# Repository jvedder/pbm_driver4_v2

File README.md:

# pdm_driver4_v2
 
PCB Design in KiCad 10 with 4 channels of high-speed, current-controlled LED drivers for a PBM Device prototype.
 
**MIT License**
 
**WARNING**: The eye safety of this device has not been established. **USE AT YOUR OWN RISK.**

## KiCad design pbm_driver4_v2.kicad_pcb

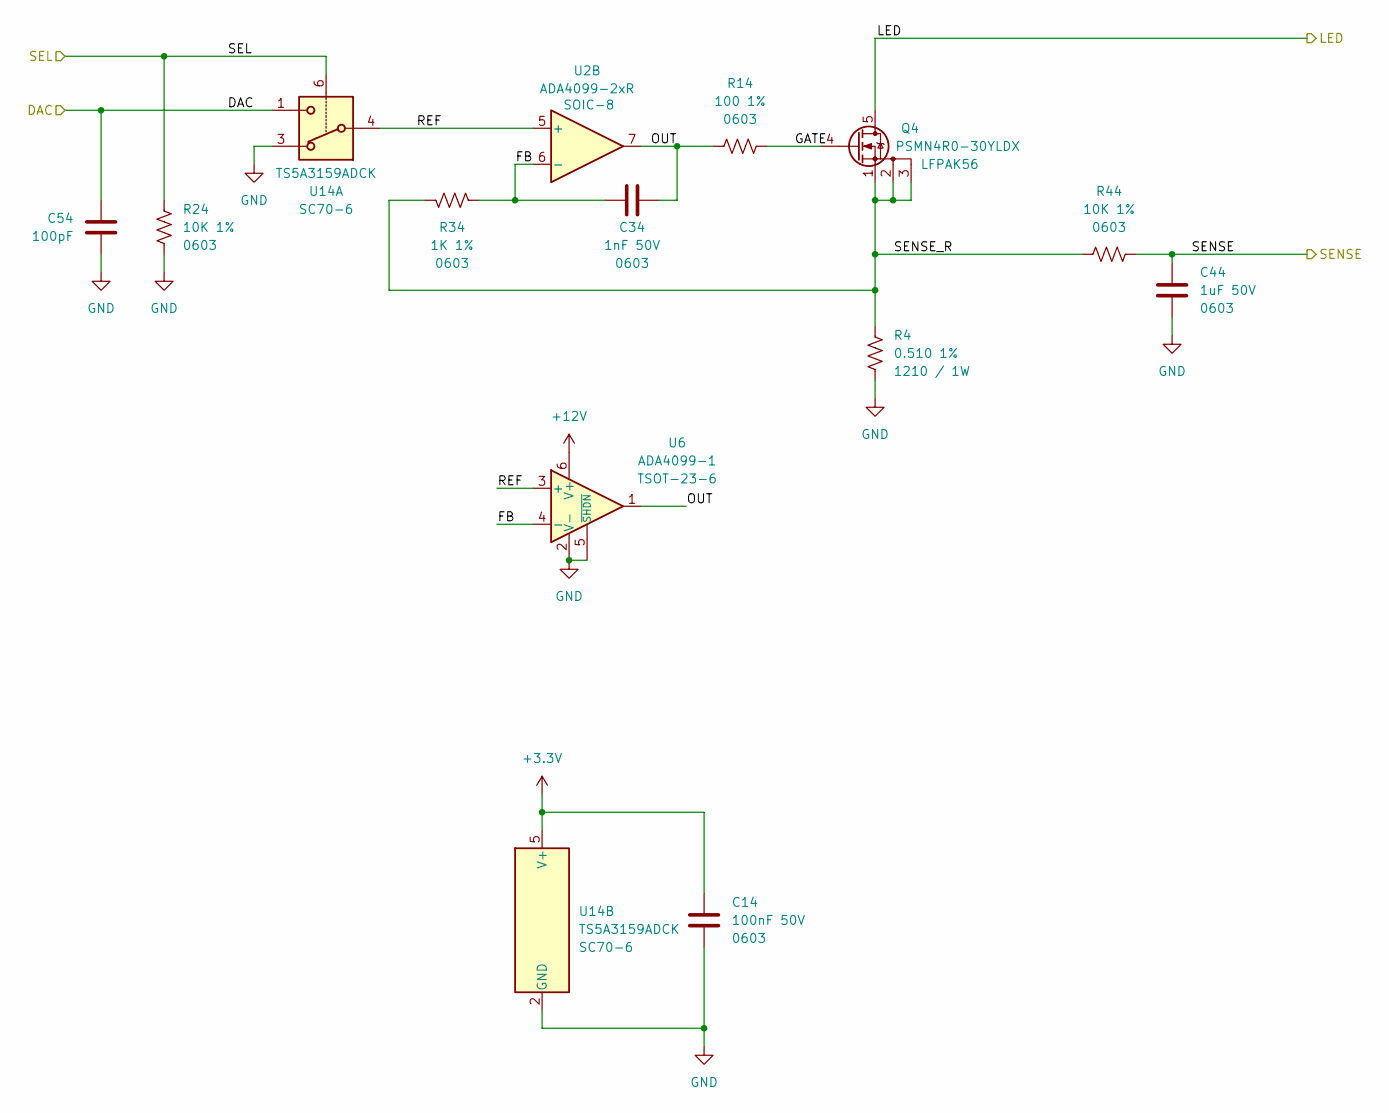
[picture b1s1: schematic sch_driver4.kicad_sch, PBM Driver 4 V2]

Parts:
C14: 100nF 50V; C_0603_1608Metric
C34: 1nF 50V; C_0603_1608Metric
C44: 1uF 50V; C_0603_1608Metric
C54: 100pF; C_0603_1608Metric
Q4: PSMN4R0-30YLDX; LFPAK56
R4: 0.510 1%; R_1210_3225Metric_Pad1.30x2.65mm_HandSolder
R14: 100 1%; R_0603_1608Metric
R24, R44: 10K 1%; R_0603_1608Metric
R34: 1K 1%; R_0603_1608Metric
U2: ADA4099-2xR; SOIC-8_3.9x4.9mm_P1.27mm; Digikey 505-ADA4099-2BRZ-ND
U6: ADA4099-1; TSOT-23-6; Digikey 505-ADA4099-1BUJZ-RL7CT-ND
U14: TS5A3159ADCK; SOT-363_SC-70-6; Digikey 296-21188-1-ND

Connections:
+3.3V: C14.1, U14.5 (V+); also elsewhere on the board
/DAC2: C54.1, U14.1; also elsewhere on the board
/Driver4/FB: C34.1, R34.2, U2.6 (-), U6.4 (-)
/Driver4/GATE: Q4.4 (G), R14.2
/Driver4/OUT: C34.2, R14.1, U2.7, U6.1
/Driver4/REF: U2.5 (+), U6.3 (+), U14.4
/Driver4/SENSE_R: Q4.1 (S), Q4.2 (S), Q4.3 (S), R4.1, R34.1, R44.2
/LED4: Q4.5 (D); also elsewhere on the board
/SEL4: R24.1, U14.6; also elsewhere on the board
/SENSE4: C44.1, R44.1; also elsewhere on the board
GND: C14.2, C44.2, C54.2, R4.2, R24.2, U6.2 (V-), U6.5 (~SHDN), U14.2 (GND), U14.3; also elsewhere on the board

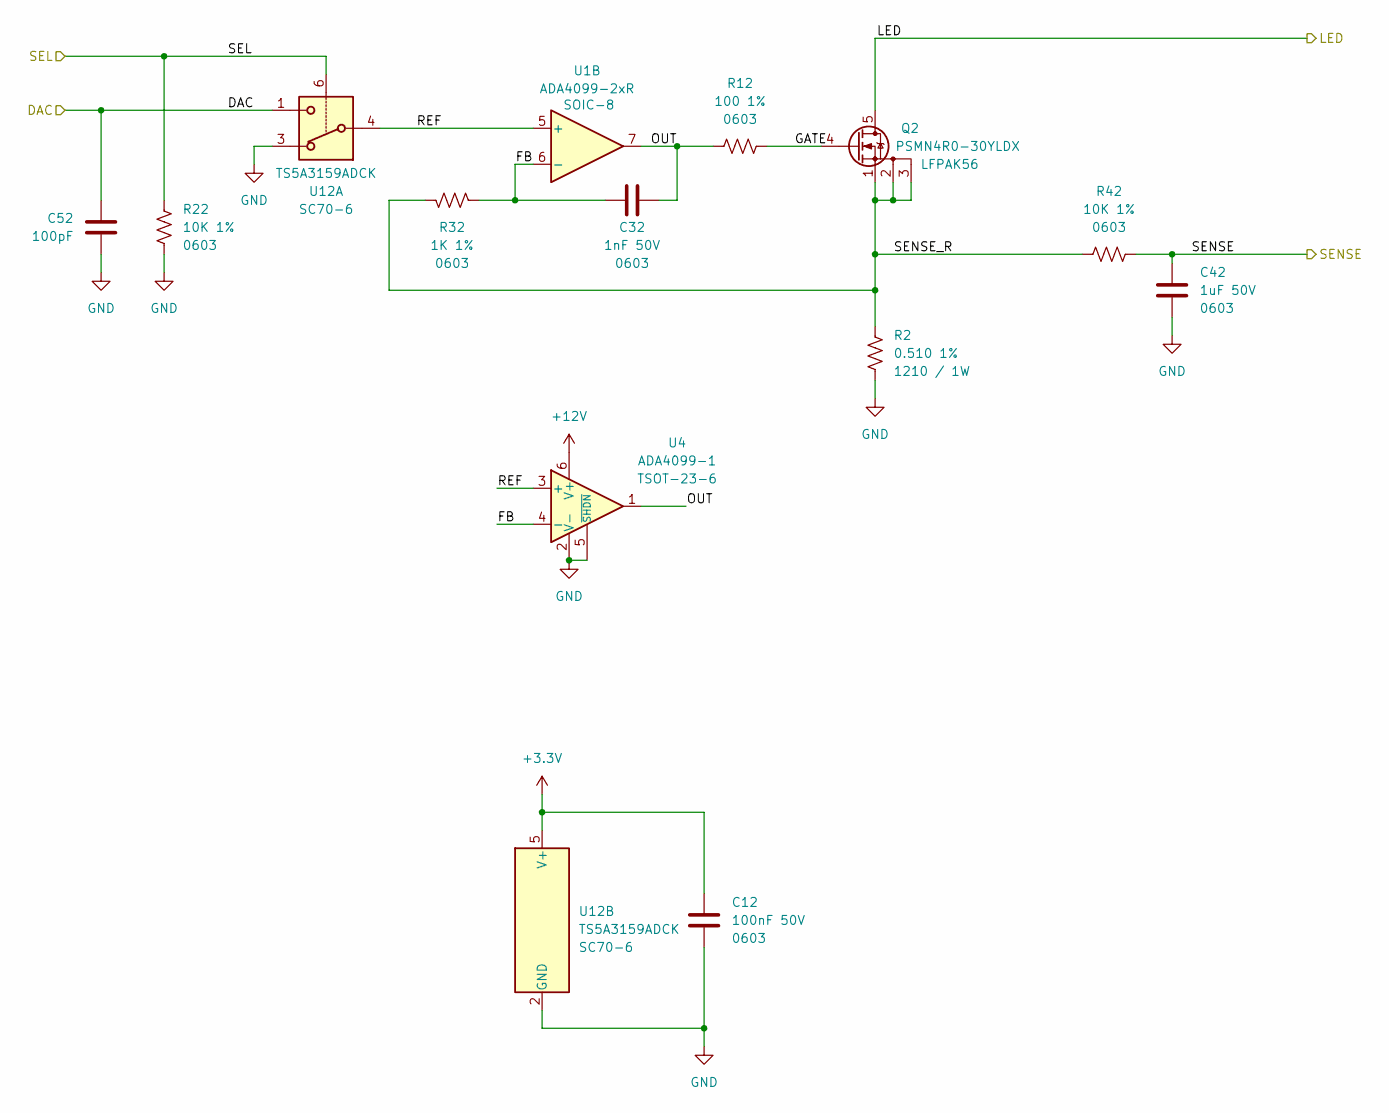
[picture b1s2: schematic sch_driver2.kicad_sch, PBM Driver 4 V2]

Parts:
C12: 100nF 50V; C_0603_1608Metric
C32: 1nF 50V; C_0603_1608Metric
C42: 1uF 50V; C_0603_1608Metric
C52: 100pF; C_0603_1608Metric
Q2: PSMN4R0-30YLDX; LFPAK56
R2: 0.510 1%; R_1210_3225Metric_Pad1.30x2.65mm_HandSolder
R12: 100 1%; R_0603_1608Metric
R22, R42: 10K 1%; R_0603_1608Metric
R32: 1K 1%; R_0603_1608Metric
U1: ADA4099-2xR; SOIC-8_3.9x4.9mm_P1.27mm; Digikey 505-ADA4099-2BRZ-ND
U4: ADA4099-1; TSOT-23-6; Digikey 505-ADA4099-1BUJZ-RL7CT-ND
U12: TS5A3159ADCK; SOT-363_SC-70-6; Digikey 296-21188-1-ND

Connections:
+3.3V: C12.1, U12.5 (V+); also elsewhere on the board
/DAC2: C52.1, U12.1; also elsewhere on the board
/Driver2/FB: C32.1, R32.2, U1.6 (-), U4.4 (-)
/Driver2/GATE: Q2.4 (G), R12.2
/Driver2/OUT: C32.2, R12.1, U1.7, U4.1
/Driver2/REF: U1.5 (+), U4.3 (+), U12.4
/Driver2/SENSE_R: Q2.1 (S), Q2.2 (S), Q2.3 (S), R2.1, R32.1, R42.2
/LED2: Q2.5 (D); also elsewhere on the board
/SEL2: R22.1, U12.6; also elsewhere on the board
/SENSE2: C42.1, R42.1; also elsewhere on the board
GND: C12.2, C42.2, C52.2, R2.2, R22.2, U4.2 (V-), U4.5 (~SHDN), U12.2 (GND), U12.3; also elsewhere on the board

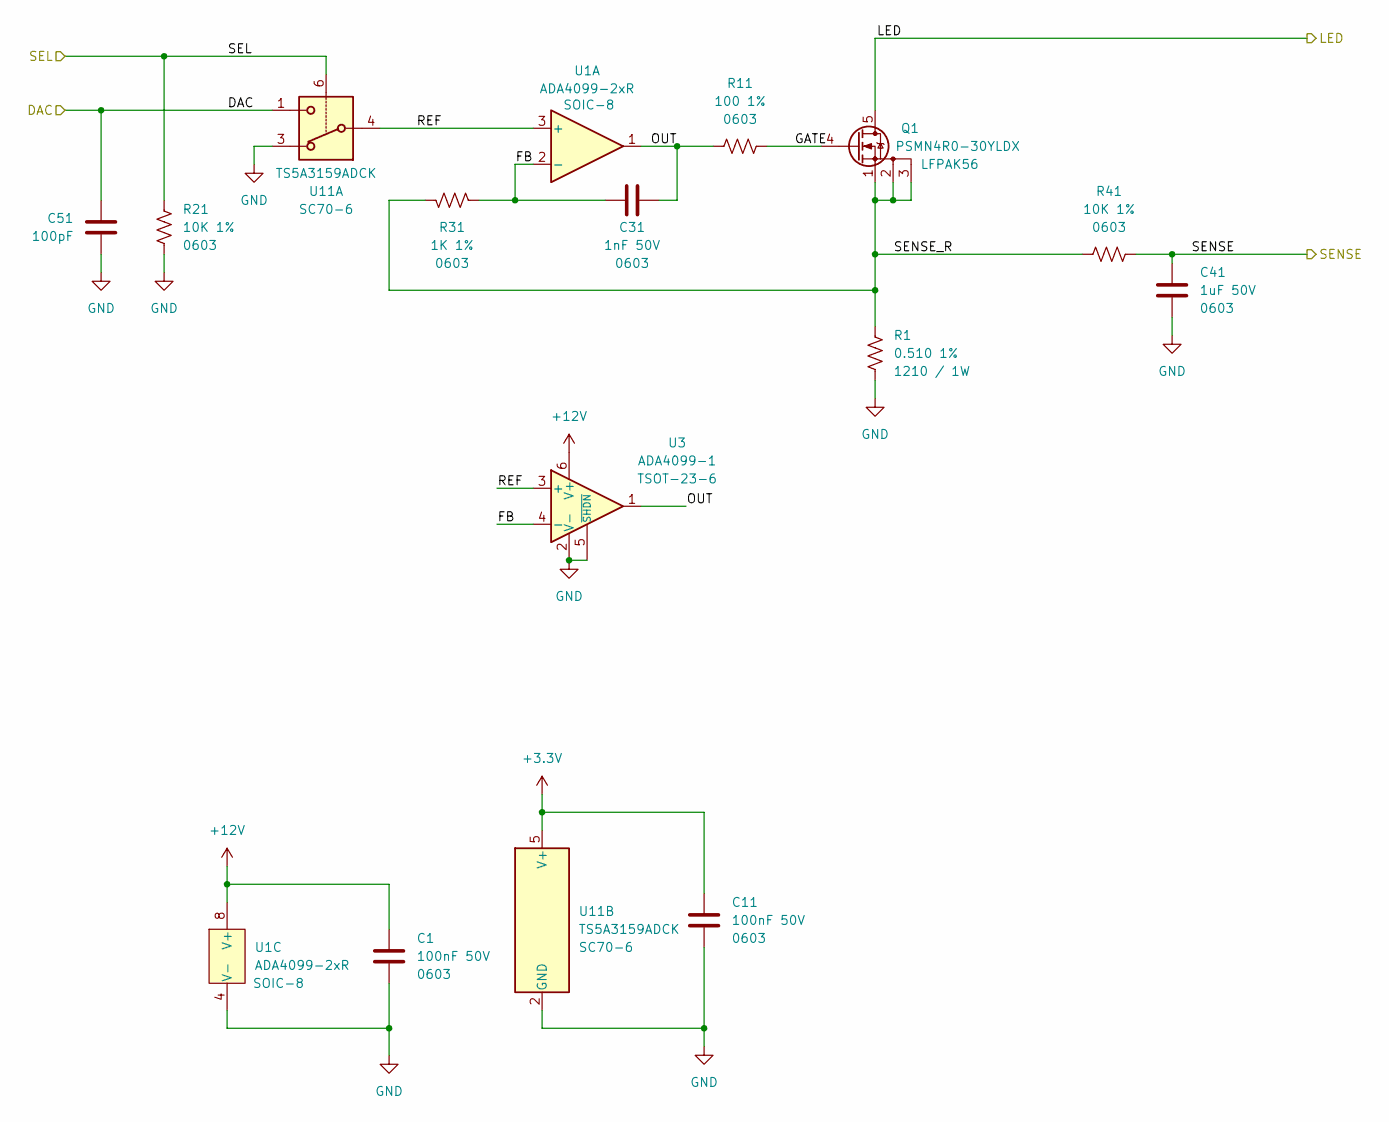
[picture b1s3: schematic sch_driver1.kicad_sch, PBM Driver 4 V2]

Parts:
C1, C11: 100nF 50V; C_0603_1608Metric
C31: 1nF 50V; C_0603_1608Metric
C41: 1uF 50V; C_0603_1608Metric
C51: 100pF; C_0603_1608Metric
Q1: PSMN4R0-30YLDX; LFPAK56
R1: 0.510 1%; R_1210_3225Metric_Pad1.30x2.65mm_HandSolder
R11: 100 1%; R_0603_1608Metric
R21, R41: 10K 1%; R_0603_1608Metric
R31: 1K 1%; R_0603_1608Metric
U1: ADA4099-2xR; SOIC-8_3.9x4.9mm_P1.27mm; Digikey 505-ADA4099-2BRZ-ND
U3: ADA4099-1; TSOT-23-6; Digikey 505-ADA4099-1BUJZ-RL7CT-ND
U11: TS5A3159ADCK; SOT-363_SC-70-6; Digikey 296-21188-1-ND

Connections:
+3.3V: C11.1, U11.5 (V+); also elsewhere on the board
+12V: C1.1, U1.8 (V+), U3.6 (V+); also elsewhere on the board
/DAC1: C51.1, U11.1; also elsewhere on the board
/Driver1/FB: C31.1, R31.2, U1.2 (-), U3.4 (-)
/Driver1/GATE: Q1.4 (G), R11.2
/Driver1/OUT: C31.2, R11.1, U1.1, U3.1
/Driver1/REF: U1.3 (+), U3.3 (+), U11.4
/Driver1/SENSE_R: Q1.1 (S), Q1.2 (S), Q1.3 (S), R1.1, R31.1, R41.2
/LED1: Q1.5 (D); also elsewhere on the board
/SEL1: R21.1, U11.6; also elsewhere on the board
/SENSE1: C41.1, R41.1; also elsewhere on the board
GND: C1.2, C11.2, C41.2, C51.2, R1.2, R21.2, U1.4 (V-), U3.2 (V-), U3.5 (~SHDN), U11.2 (GND), U11.3; also elsewhere on the board

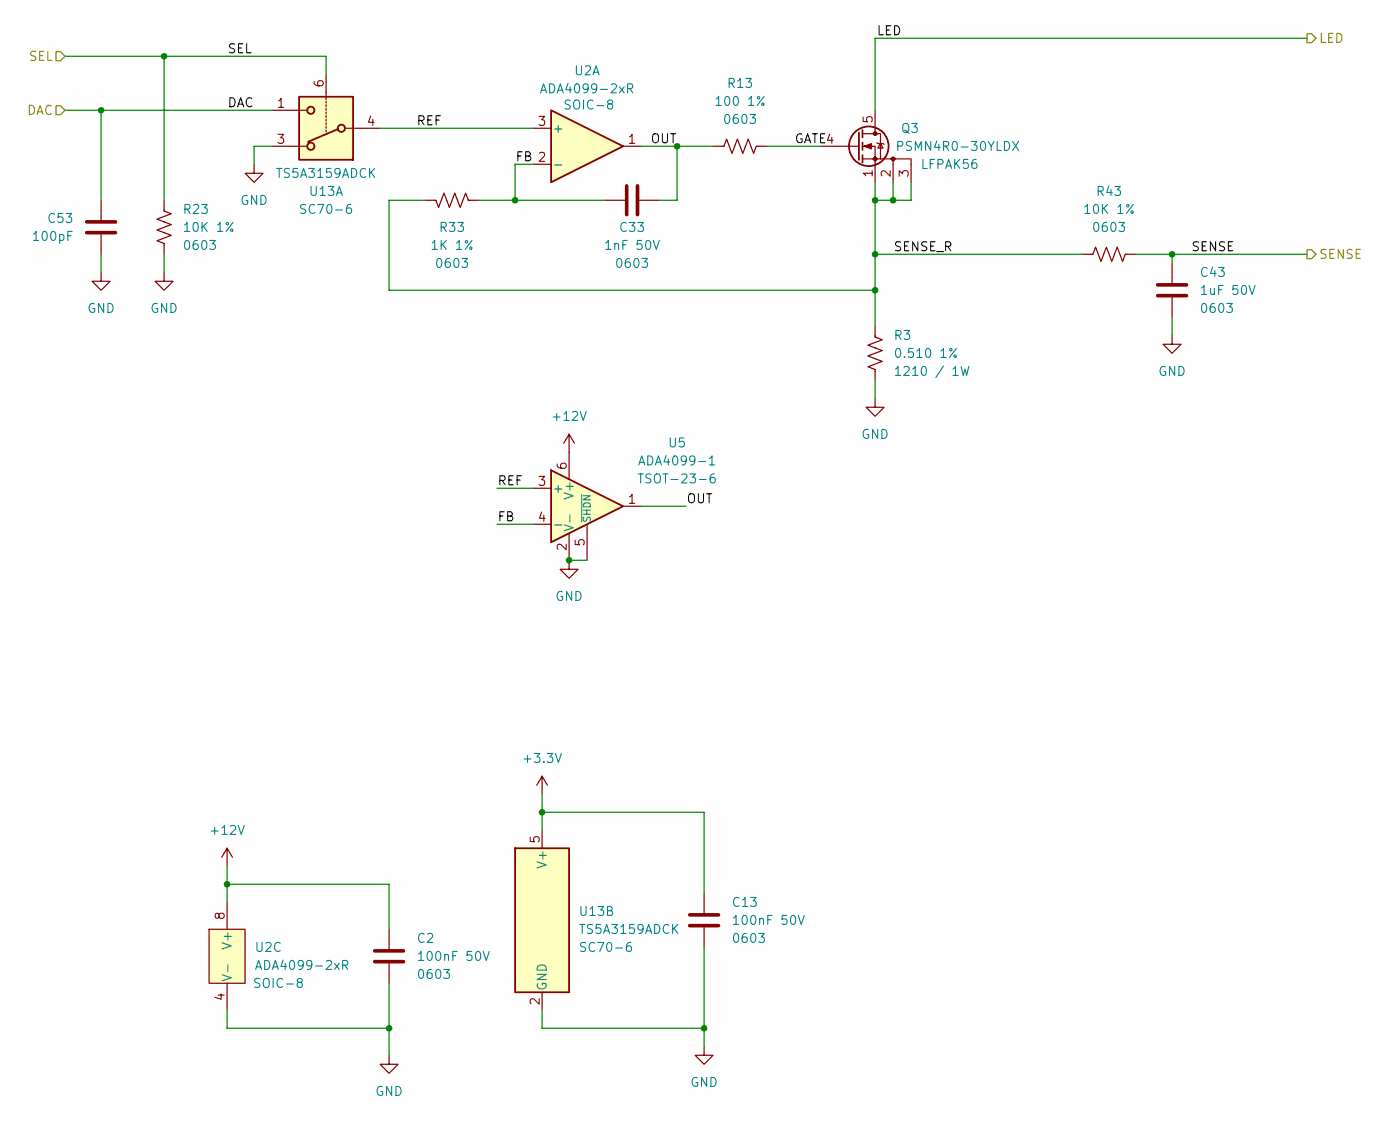
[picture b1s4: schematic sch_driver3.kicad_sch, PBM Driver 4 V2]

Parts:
C2, C13: 100nF 50V; C_0603_1608Metric
C33: 1nF 50V; C_0603_1608Metric
C43: 1uF 50V; C_0603_1608Metric
C53: 100pF; C_0603_1608Metric
Q3: PSMN4R0-30YLDX; LFPAK56
R3: 0.510 1%; R_1210_3225Metric_Pad1.30x2.65mm_HandSolder
R13: 100 1%; R_0603_1608Metric
R23, R43: 10K 1%; R_0603_1608Metric
R33: 1K 1%; R_0603_1608Metric
U2: ADA4099-2xR; SOIC-8_3.9x4.9mm_P1.27mm; Digikey 505-ADA4099-2BRZ-ND
U5: ADA4099-1; TSOT-23-6; Digikey 505-ADA4099-1BUJZ-RL7CT-ND
U13: TS5A3159ADCK; SOT-363_SC-70-6; Digikey 296-21188-1-ND

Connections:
+3.3V: C13.1, U13.5 (V+); also elsewhere on the board
+12V: C2.1, U2.8 (V+), U5.6 (V+); also elsewhere on the board
/DAC1: C53.1, U13.1; also elsewhere on the board
/Driver3/FB: C33.1, R33.2, U2.2 (-), U5.4 (-)
/Driver3/GATE: Q3.4 (G), R13.2
/Driver3/OUT: C33.2, R13.1, U2.1, U5.1
/Driver3/REF: U2.3 (+), U5.3 (+), U13.4
/Driver3/SENSE_R: Q3.1 (S), Q3.2 (S), Q3.3 (S), R3.1, R33.1, R43.2
/LED3: Q3.5 (D); also elsewhere on the board
/SEL3: R23.1, U13.6; also elsewhere on the board
/SENSE3: C43.1, R43.1; also elsewhere on the board
GND: C2.2, C13.2, C43.2, C53.2, R3.2, R23.2, U2.4 (V-), U5.2 (V-), U5.5 (~SHDN), U13.2 (GND), U13.3; also elsewhere on the board

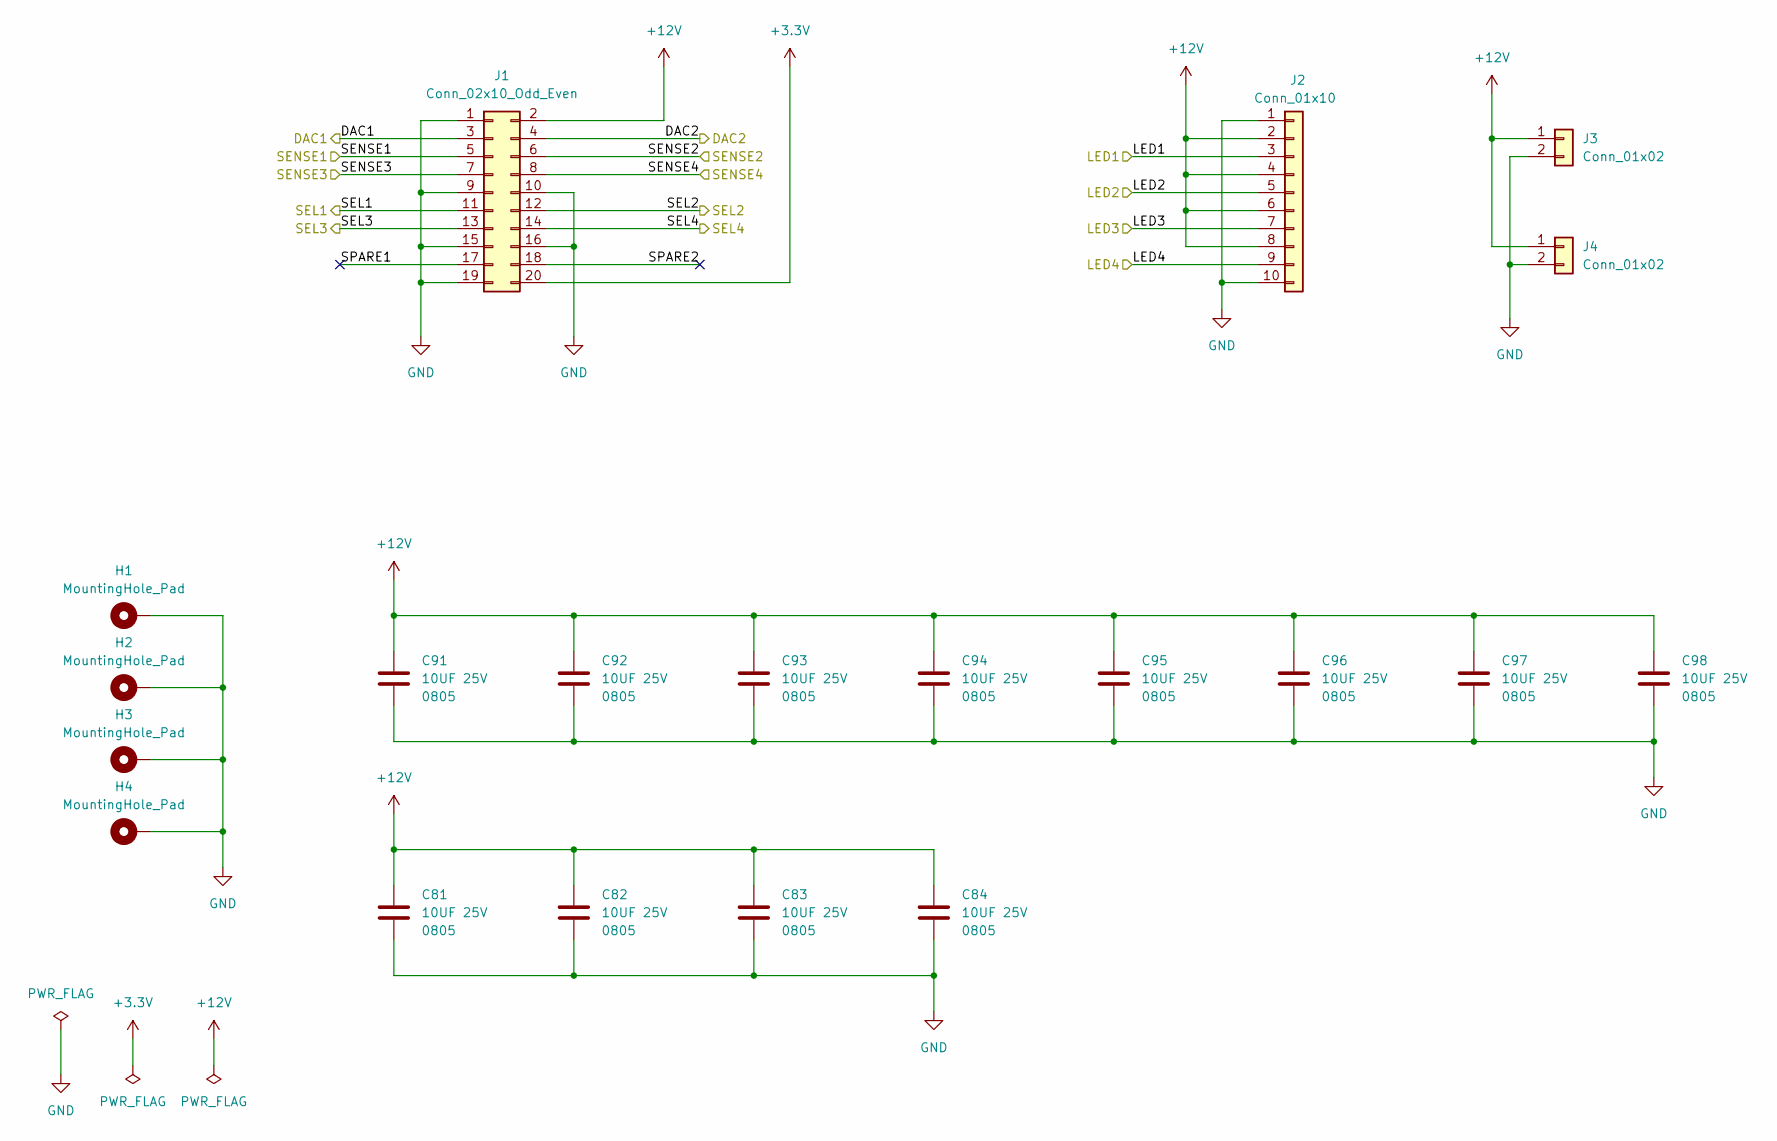
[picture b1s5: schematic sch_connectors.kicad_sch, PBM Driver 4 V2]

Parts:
C81, C82, C83, C84, C91, C92, C93, C94, C95, C96, C97, C98: 10UF 25V; C_0805_2012Metric
H1, H2, H3, H4: MountingHole_Pad; MountingHole_3.2mm_M3_Pad
J1: Conn_02x10_Odd_Even; PinHeader_2x10_P2.54mm_Vertical
J2: Conn_01x10; PinHeader_1x10_P2.54mm_Vertical
J3, J4: Conn_01x02; PinHeader_1x02_P2.54mm_Vertical

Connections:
+3.3V: J1.20; also elsewhere on the board
+12V: C81.1, C82.1, C83.1, C84.1, C91.1, C92.1, C93.1, C94.1, C95.1, C96.1, C97.1, C98.1, J1.2, J2.2, J2.4, J2.6, J2.8, J3.1, J4.1; also elsewhere on the board
/Connectors/SPARE1: J1.17
/Connectors/SPARE2: J1.18
/DAC1: J1.3; also elsewhere on the board
/DAC2: J1.4; also elsewhere on the board
/LED1: J2.3; also elsewhere on the board
/LED2: J2.5; also elsewhere on the board
/LED3: J2.7; also elsewhere on the board
/LED4: J2.9; also elsewhere on the board
/SEL1: J1.11; also elsewhere on the board
/SEL2: J1.12; also elsewhere on the board
/SEL3: J1.13; also elsewhere on the board
/SEL4: J1.14; also elsewhere on the board
/SENSE1: J1.5; also elsewhere on the board
/SENSE2: J1.6; also elsewhere on the board
/SENSE3: J1.7; also elsewhere on the board
/SENSE4: J1.8; also elsewhere on the board
GND: C81.2, C82.2, C83.2, C84.2, C91.2, C92.2, C93.2, C94.2, C95.2, C96.2, C97.2, C98.2, H1.1 (1_1), H2.1 (1_1), H3.1 (1_1), H4.1 (1_1), J1.1, J1.9, J1.10, J1.15, J1.16, J1.19, J2.1, J2.10, J3.2, J4.2; also elsewhere on the board

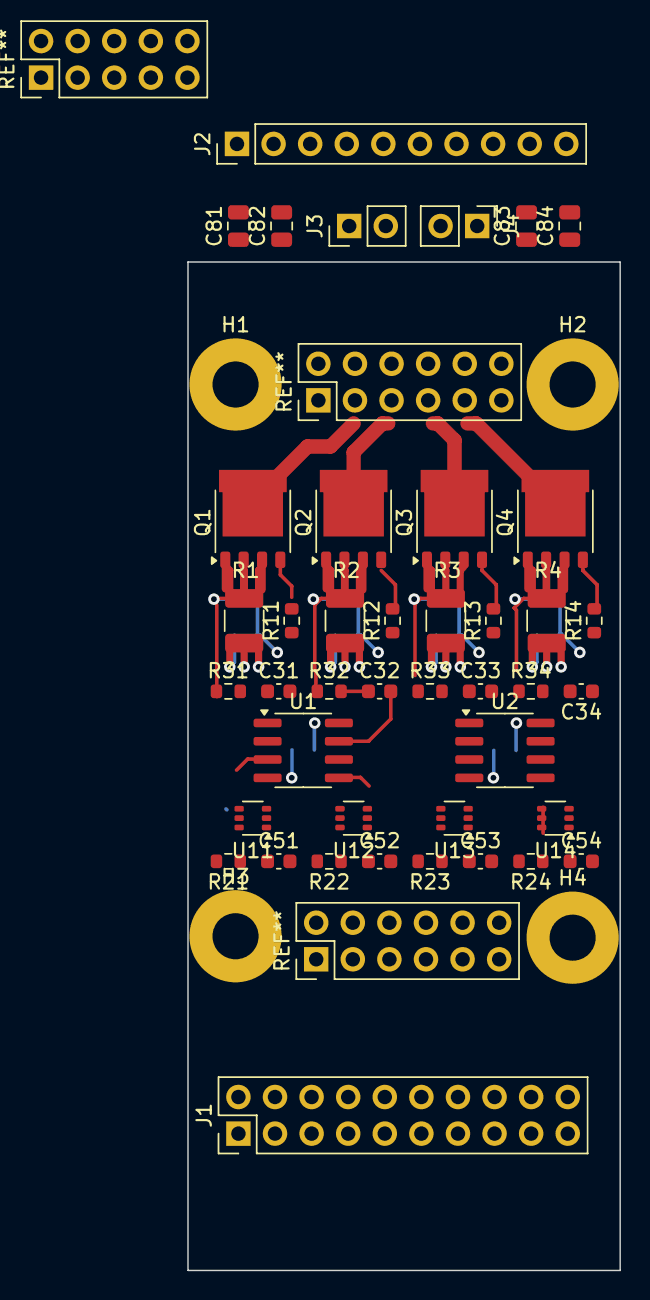
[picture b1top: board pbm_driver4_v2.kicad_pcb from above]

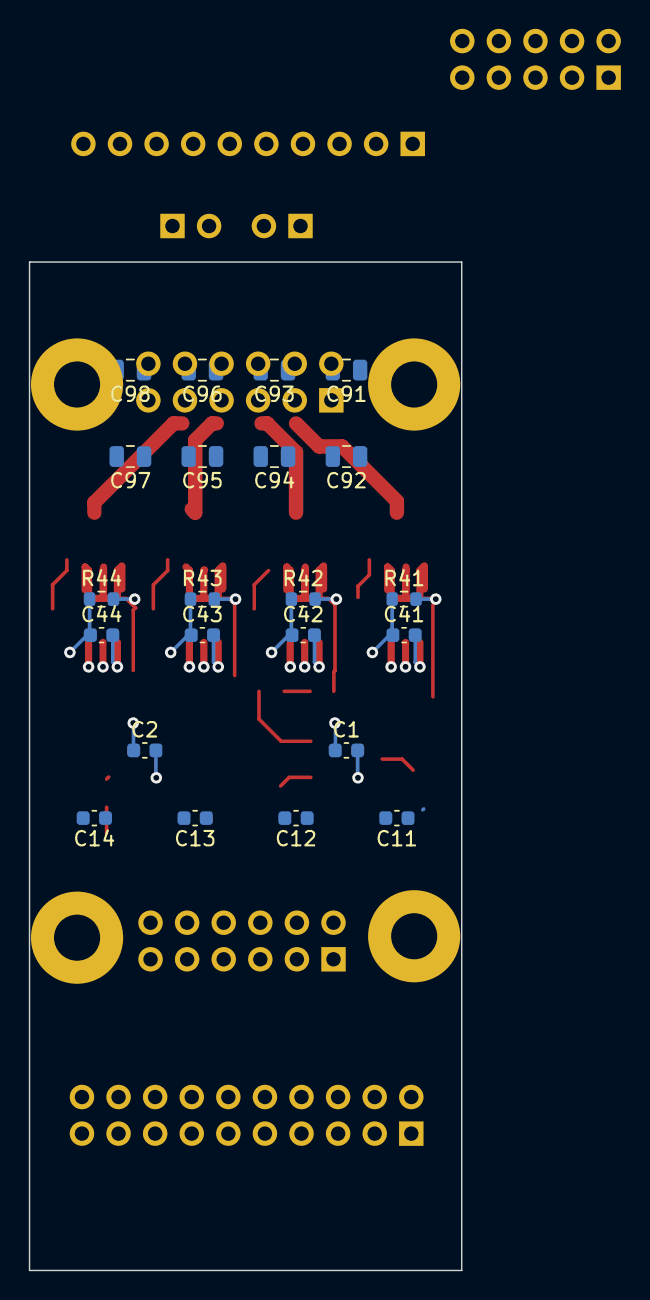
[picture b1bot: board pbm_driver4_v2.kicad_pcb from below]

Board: 4 copper layers, 30.0 x 70.0 mm, 68 parts (22 on the bottom side), 37 nets.

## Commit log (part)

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2025-08-22 WIP Redraw in KiCad 9
2025-12-06 WIP - Updating analog switch
2025-12-07 New analog switch drawn. Updated page borders to B-size sheets.
2025-12-08 Added buffers to current sense signals
2025-12-08 Updated 'Size' property to 'Package' on R & C. Cleaned up switch page.
2025-12-08 renamed 'power_switch' schematic sheet to 'power'
2025-12-08 Misc schematic cleanup. Fix ERC errors and warnings
2025-12-24 Added active LP filter to sense signals. First pass of part placement on 30x70 mm PCB.
2025-12-25 Refactor driver schematic sheet into four A-size pages.
2025-12-25 Add PCB file to refactor.
2025-12-25 Finished schematic refactor to six A-sheets. Updated PCB.
2025-12-27 Updated PCB stackup and design options
2025-12-27 Added two 1x2 12V power connectors and 4x bypassing caps
2025-12-28 Routing WIP
2025-12-29 Routing WIP. Prep to look at SOT-23 op amps for U1 and U2. Added convenience link to Git Bash.
2025-12-30 Routing WIP with SOT-23 op amps
2026-01-02 Exploring op amp rounting options.
2026-01-03 Added pull-downs to output of Sense filter op amps
2026-01-07 Added SOT-23 foorptints to lib. Update courtyard on 0603 to 3.3 x 1.8 mm
2026-01-07 Change schematic sense buffer vrom OPA333 in SC70 to OPA365 in SOT-23
2026-01-07 Add start of design notes
2026-01-07 WIP routing and placement with OPA365
2026-01-20 Top side only placement and routing figured out (Channel 1).

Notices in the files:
sch_connectors.kicad_sch:
Copyright (c) 2025 John Vedder
